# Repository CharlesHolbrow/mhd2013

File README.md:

mhd2013
=======

Music Hack Day 2013

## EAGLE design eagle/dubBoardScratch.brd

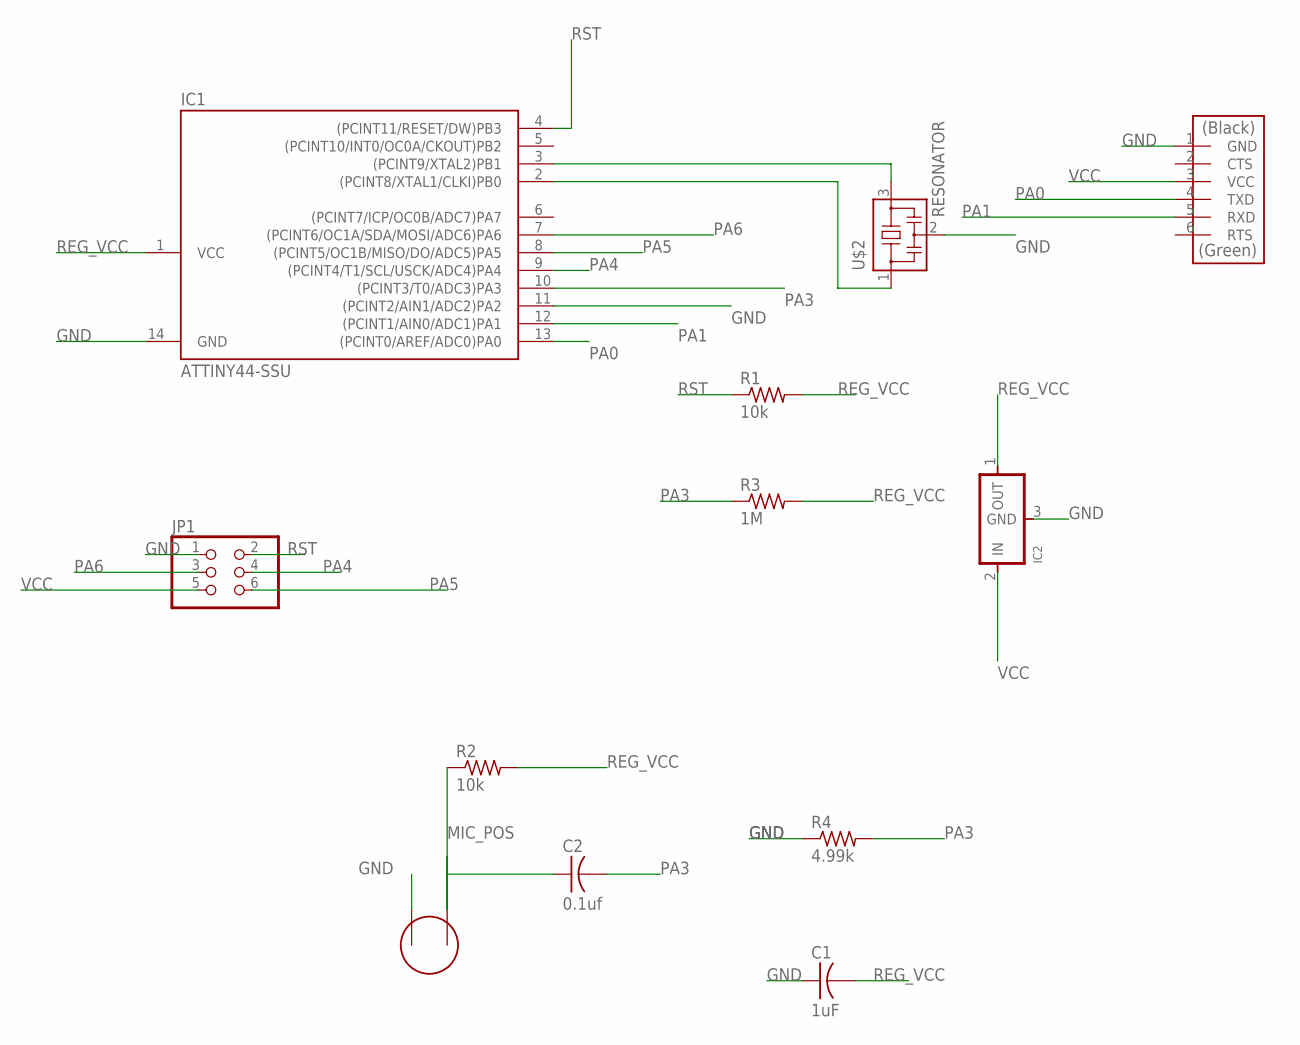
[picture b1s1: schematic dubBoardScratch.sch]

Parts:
C1: 1uF; C1206FAB
C2: 0.1uf; C1206FAB
IC1: ATTINY44-SSU; SOIC14
IC2: REGULATORSOT23; SOT23
JP1: PINHD-2X3-SMD; 2X03SMD
R1, R2: 10k; R1206FAB
R3: 1M; R1206FAB
R4: 4.99k; R1206FAB
U$1: FTDI-SMD-HEADER; 1X06SMD
U$2: RESONATOR; EFOBM
U$3: ELECTRET; ELECTRET_2742PBJ-A

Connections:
GND: C1.1, IC1.11 ((PCINT2/AIN1/ADC2)PA2), IC1.14 (GND), IC2.3 (GND), JP1.1, R4.1, U$1.1 (GND), U$2.2, U$3.P$2
MIC_POS: C2.1, R2.1, U$3.P$1
unnamed: IC1.3 ((PCINT9/XTAL2)PB1), U$2.3
unnamed: IC1.2 ((PCINT8/XTAL1/CLKI)PB0), U$2.1
PA0: IC1.13 ((PCINT0/AREF/ADC0)PA0), U$1.4 (TXD)
PA1: IC1.12 ((PCINT1/AIN0/ADC1)PA1), U$1.5 (RXD)
PA3: C2.2, IC1.10 ((PCINT3/T0/ADC3)PA3), R3.1, R4.2
PA4: IC1.9 ((PCINT4/T1/SCL/USCK/ADC4)PA4), JP1.4
PA5: IC1.8 ((PCINT5/OC1B/MISO/DO/ADC5)PA5), JP1.6
PA6: IC1.7 ((PCINT6/OC1A/SDA/MOSI/ADC6)PA6), JP1.3
REG_VCC: C1.2, IC1.1 (VCC), IC2.1 (OUT), R1.2, R2.2, R3.2
RST: IC1.4 ((PCINT11/RESET/DW)PB3), JP1.2, R1.1
VCC: IC2.2 (IN), JP1.5, U$1.3 (VCC)

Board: 2 copper layers, 12 parts (0 on the bottom side), 13 nets, no tracks yet.

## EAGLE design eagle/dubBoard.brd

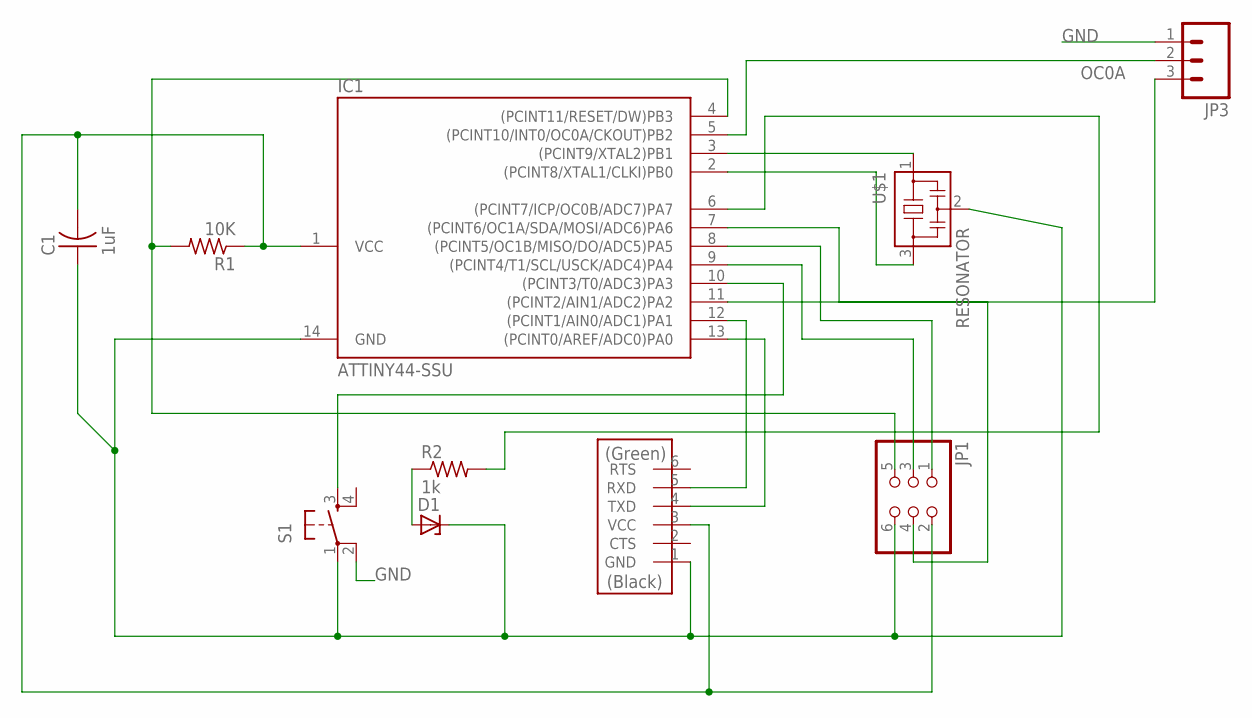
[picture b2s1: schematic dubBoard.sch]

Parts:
C1: 1uF; C1206FAB
D1: ZENER_DIODESOD123; SOD123
IC1: ATTINY44-SSU; SOIC14
JP1: PINHD-2X3-SMD; 2X03SMD
JP3: M03SMD_RA_MALE; 1X03_SMD_RA_MALE
R1: 10K; R1206
R2: 1k; R1206FAB
S1: 6MM_SWITCH6MM_SWITCH; 6MM_SWITCH
U$1: RESONATOR; EFOBM
U$2: FTDI-SMD-HEADER; 1X06SMD

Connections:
GND: C1.1, D1.CATHODE, IC1.14 (GND), JP1.6, JP3.1, S1.1, S1.2 (P1), U$1.2, U$2.1 (GND)
unnamed: D1.ANODE, R2.1
unnamed: IC1.2 ((PCINT8/XTAL1/CLKI)PB0), U$1.3
unnamed: IC1.3 ((PCINT9/XTAL2)PB1), U$1.1
unnamed: C1.2, IC1.1 (VCC), JP1.2, R1.1, U$2.3 (VCC)
unnamed: IC1.4 ((PCINT11/RESET/DW)PB3), JP1.5, R1.2
unnamed: IC1.8 ((PCINT5/OC1B/MISO/DO/ADC5)PA5), JP1.1
unnamed: IC1.9 ((PCINT4/T1/SCL/USCK/ADC4)PA4), JP1.3
unnamed: IC1.10 ((PCINT3/T0/ADC3)PA3), S1.3 (S)
unnamed: IC1.7 ((PCINT6/OC1A/SDA/MOSI/ADC6)PA6), JP1.4
unnamed: IC1.6 ((PCINT7/ICP/OC0B/ADC7)PA7), R2.2
unnamed: IC1.13 ((PCINT0/AREF/ADC0)PA0), U$2.4 (TXD)
unnamed: IC1.12 ((PCINT1/AIN0/ADC1)PA1), U$2.5 (RXD)
unnamed: IC1.11 ((PCINT2/AIN1/ADC2)PA2), JP3.3
OC0A: IC1.5 ((PCINT10/INT0/OC0A/CKOUT)PB2), JP3.2

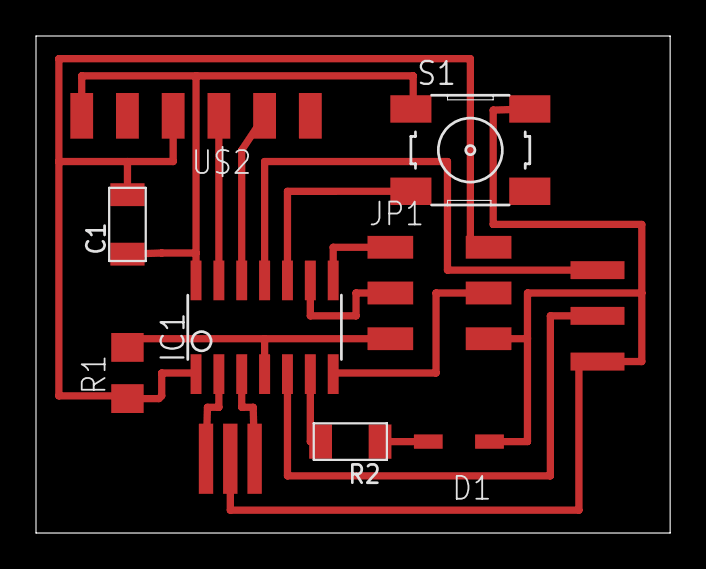
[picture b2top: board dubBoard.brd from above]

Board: 2 copper layers, 35.2 x 27.6 mm, 10 parts (0 on the bottom side), 15 nets.

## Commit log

2013-11-09 Add attiny datasheet
2013-11-09 Example
2013-11-09 More examples, and .gitignore
2013-11-09 adding code for audio generation
2013-11-10 dbBoardScratch has audio input
2013-11-10 board
2013-11-10 add pictures

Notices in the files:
parts and their libraries:
SparkFun-Connectors: Licensing: CC v3.0 Share-Alike You are welcome to use this library for commercial purposes.
